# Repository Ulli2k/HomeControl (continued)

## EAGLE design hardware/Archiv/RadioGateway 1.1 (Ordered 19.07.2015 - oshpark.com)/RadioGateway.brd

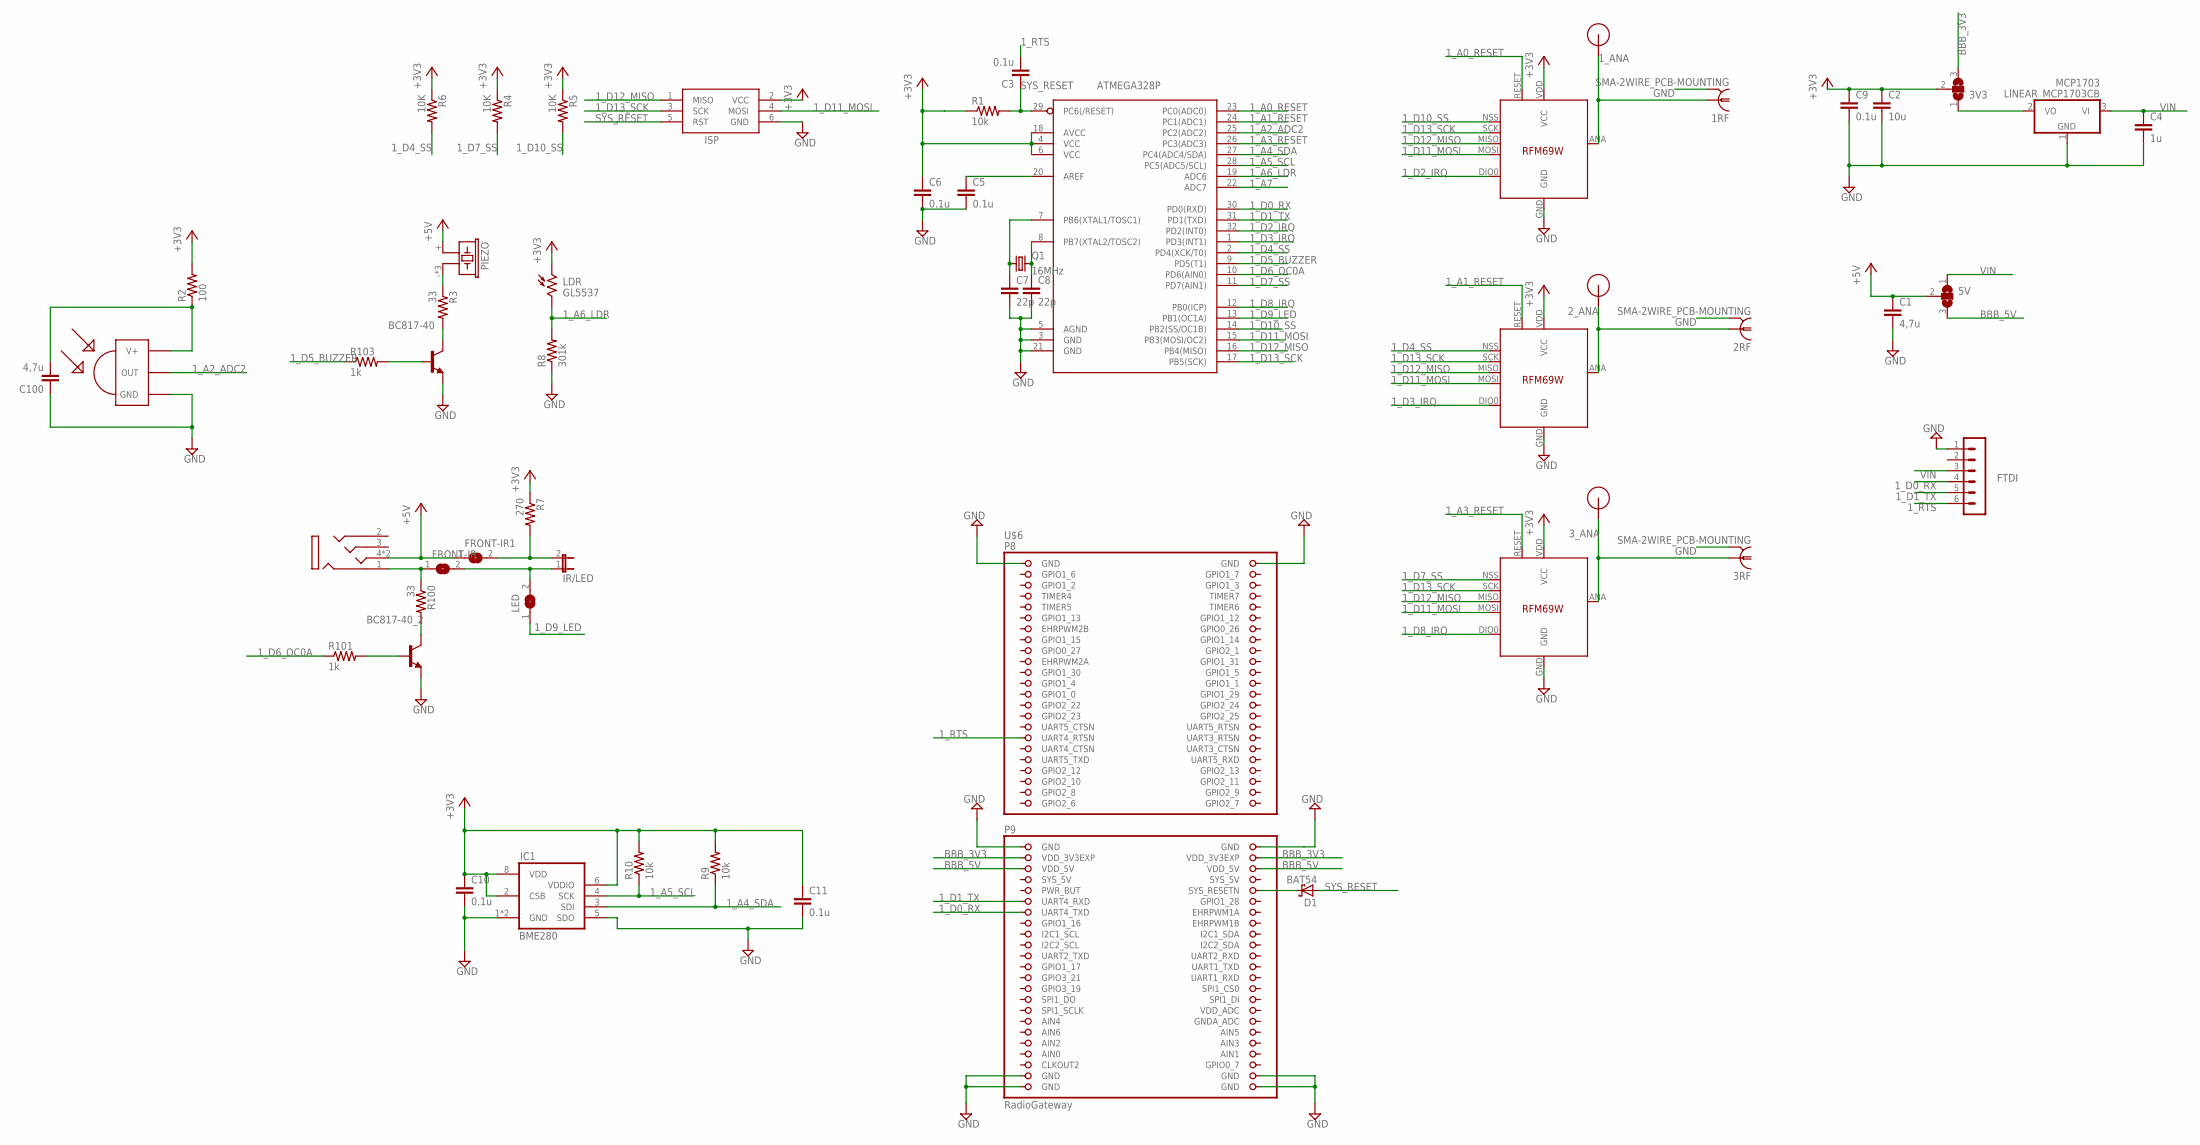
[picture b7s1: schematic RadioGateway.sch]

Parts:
1RF, 2RF, 3RF: SMA-2WIRE_PCB-MOUNTING; J01151A0931
1_RFM69, 2_RFM69, 3_RFM69: RFM69_MINIPADS; RFM69W-MINPADS
3V3, 5V: SJ2W; SJ_2
ATMEGA328P: ATMega-328; TQFP32-08
BC817-40, BC817-40_2: BC817-40-NPN-SOT23-BEC; SOT23-BEC
C1, C100: 4,7u; 0603-CAP
C2: 10u; 0603-CAP
C3, C5, C6, C9, C10, C11: 0.1u; 0603-CAP
C4: 1u; 0603-CAP
C7, C8: 22p; 0603-CAP
D1: BAT54; SOT23
FRONT-IR, FRONT-IR1: SJ
FTDI: FTDI; MA06-1
IC1: BME280
IR-RX: TSOP4836; TSOP18XX
IR-TX: 1503_13; 1503-03
IR/LED: JP1E; JP1
ISP: AVRISP-6; AVRISP
LDR: GL5537; M9960
LED: SJ
MCP1703: LINEAR_MCP1703CB; LINEAR_SOT23
PIEZO: BUZZER-PIEZO_SMD
Q1: 16MHz; HC49/S
R1, R9, R10: 10k; 0603-RES
R2: 100; 0603-RES
R3, R100: 33; 0603-RES
R4, R5, R6: 10K; 0603-RES
R7: 270; 0603-RES
R8: 301k; 0603-RES
R101, R103: 1k; 0603-RES
U$1, U$2, U$5: RFM12B_ANTENNA; RFM12B-ANTENNA
U$6: RadioGateway; BEAGLEBONE_SHIELD

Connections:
1_A0_RESET: 1_RFM69.RESET, ATMEGA328P.23 (PC0(ADC0))
1_A1_RESET: 2_RFM69.RESET, ATMEGA328P.24 (PC1(ADC1))
1_A2_ADC2: ATMEGA328P.25 (PC2(ADC2)), IR-RX.OUT
1_A3_RESET: 3_RFM69.RESET, ATMEGA328P.26 (PC3(ADC3))
1_A4_SDA: ATMEGA328P.27 (PC4(ADC4/SDA)), IC1.3 (SDI), R9.1
1_A5_SCL: ATMEGA328P.28 (PC5(ADC5/SCL)), IC1.4 (SCK), R10.1
1_A6_LDR: ATMEGA328P.19 (ADC6), LDR.2, R8.2
1_A7: ATMEGA328P.22 (ADC7)
1_ANA: 1RF.1, 1_RFM69.ANA (ANT), U$1.P$1
1_AREF: ATMEGA328P.20 (AREF), C5.1
1_D0_RX: ATMEGA328P.30 (PD0(RXD)), FTDI.4, U$6.59 (UART4_TXD)
1_D1_TX: ATMEGA328P.31 (PD1(TXD)), FTDI.5, U$6.57 (UART4_RXD)
1_D2_IRQ: 1_RFM69.DIO0 (DIO0/IRQ), ATMEGA328P.32 (PD2(INT0))
1_D3_IRQ: 2_RFM69.DIO0 (DIO0/IRQ), ATMEGA328P.1 (PD3(INT1))
1_D4_SS: 2_RFM69.NSS (SEL), ATMEGA328P.2 (PD4(XCK/T0)), R6.2
1_D5_BUZZER: ATMEGA328P.9 (PD5(T1)), R103.1
1_D6_OC0A: ATMEGA328P.10 (PD6(AIN0)), R101.1
1_D7_SS: 3_RFM69.NSS (SEL), ATMEGA328P.11 (PD7(AIN1)), R4.2
1_D8_IRQ: 3_RFM69.DIO0 (DIO0/IRQ), ATMEGA328P.12 (PB0(ICP))
1_D9_LED: ATMEGA328P.13 (PB1(OC1A)), LED.1
1_D10_SS: 1_RFM69.NSS (SEL), ATMEGA328P.14 (PB2(SS/OC1B)), R5.2
1_D11_MOSI: 1_RFM69.MOSI, 2_RFM69.MOSI, 3_RFM69.MOSI, ATMEGA328P.15 (PB3(MOSI/OC2)), ISP.4 (MOSI)
1_D12_MISO: 1_RFM69.MISO, 2_RFM69.MISO, 3_RFM69.MISO, ATMEGA328P.16 (PB4(MISO)), ISP.1 (MISO)
1_D13_SCK: 1_RFM69.SCK, 2_RFM69.SCK, 3_RFM69.SCK, ATMEGA328P.17 (PB5(SCK)), ISP.3 (SCK)
1_RTS: C3.2, FTDI.6, U$6.33 (UART4_RTSN)
2_ANA: 2RF.1, 2_RFM69.ANA (ANT), U$5.P$1
3_ANA: 3RF.1, 3_RFM69.ANA (ANT), U$2.P$1
+3V3: 1_RFM69.VDD (VCC), 2_RFM69.VDD (VCC), 3V3.2, 3_RFM69.VDD (VCC), ATMEGA328P.4 (VCC), ATMEGA328P.6 (VCC), ATMEGA328P.18 (AVCC), C2.1, C6.1, C9.1, C10.1, C11.1, IC1.2 (CSB), IC1.6 (VDDIO), IC1.8 (VDD), ISP.2 (VCC), LDR.1, R1.1, R2.2, R4.1, R5.1, R6.1, R7.1, R9.2, R10.2
+5V: 5V.2, C1.1, FRONT-IR1.1, IR-TX.4, IR-TX.4-2 (4), PIEZO.+ (1)
AIN0: U$6.85 (AIN0)
BBB_3V3: 3V3.3, U$6.49 (VDD_3V3EXP), U$6.50 (VDD_3V3EXP)
BBB_5V: 5V.3, U$6.51 (VDD_5V), U$6.52 (VDD_5V)
GND: 1RF.G@1 (2), 1RF.G@2 (2), 1RF.G@3 (2), 1RF.G@4 (2), 1_RFM69.GND, 2RF.G@1 (2), 2RF.G@2 (2), 2RF.G@3 (2), 2RF.G@4 (2), 2_RFM69.GND, 3RF.G@1 (2), 3RF.G@2 (2), 3RF.G@3 (2), 3RF.G@4 (2), 3_RFM69.GND, ATMEGA328P.3 (GND), ATMEGA328P.5 (AGND), ATMEGA328P.21 (GND), BC817-40.E, BC817-40_2.E, C1.2, C2.2, C4.2, C5.2, C6.2, C7.2, C8.2, C9.2, C10.2, C11.2, C100.1, FTDI.1, IC1.1 (GND), IC1.5 (SDO), IC1.7 (GND), IR-RX.GND, ISP.6 (GND), MCP1703.1 (GND), R8.1, U$6.1 (GND), U$6.2 (GND), U$6.47 (GND), U$6.48 (GND), U$6.89 (GND), U$6.90 (GND), U$6.91 (GND), U$6.92 (GND)
unnamed: ATMEGA328P.7 (PB6(XTAL1/TOSC1)), C7.1, Q1.1
unnamed: PIEZO.- (2), PIEZO.DUMMY (2), PIEZO.DUMMY1 (2), R3.1
unnamed: FRONT-IR.1, IR-TX.1, R100.1
unnamed: BC817-40_2.C, R100.2
unnamed: D1.3 (C), U$6.56 (SYS_RESETN)
unnamed: 3V3.1, MCP1703.2 (VO)
unnamed: ATMEGA328P.8 (PB7(XTAL2/TOSC2)), C8.1, Q1.2
unnamed: BC817-40.C, R3.2
unnamed: FRONT-IR.2, IR/LED.1, LED.2
unnamed: FRONT-IR1.2, IR/LED.2, R7.2
unnamed: BC817-40.B, R103.2
unnamed: C100.2, IR-RX.VCC (V+), R2.1
unnamed: BC817-40_2.B, R101.2
SYS_5V: U$6.53 (SYS_5V)
SYS_RESET: ATMEGA328P.29 (PC6(/RESET)), C3.1, D1.1 (A), ISP.5 (RST), R1.2
VIN: 5V.1, C4.1, FTDI.3, MCP1703.3 (VI)

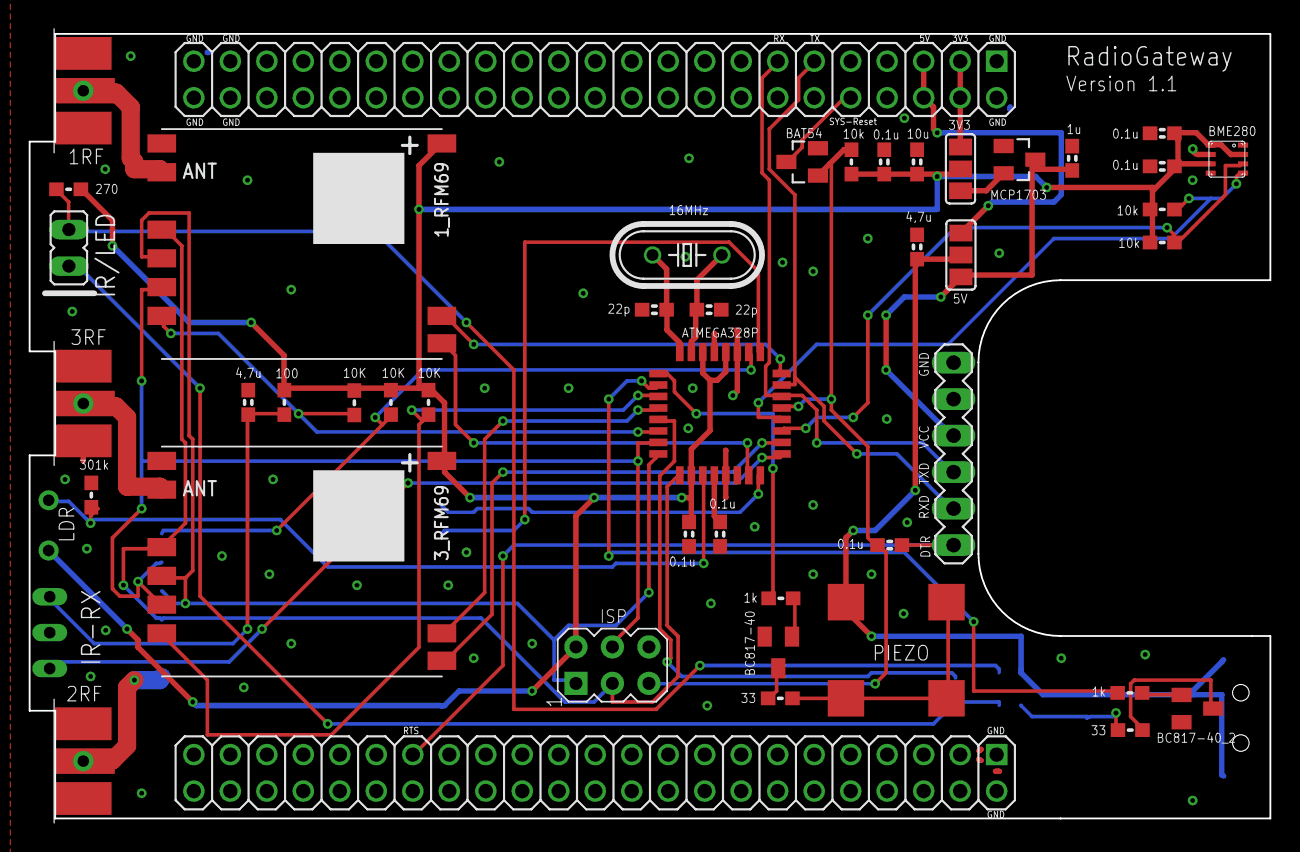
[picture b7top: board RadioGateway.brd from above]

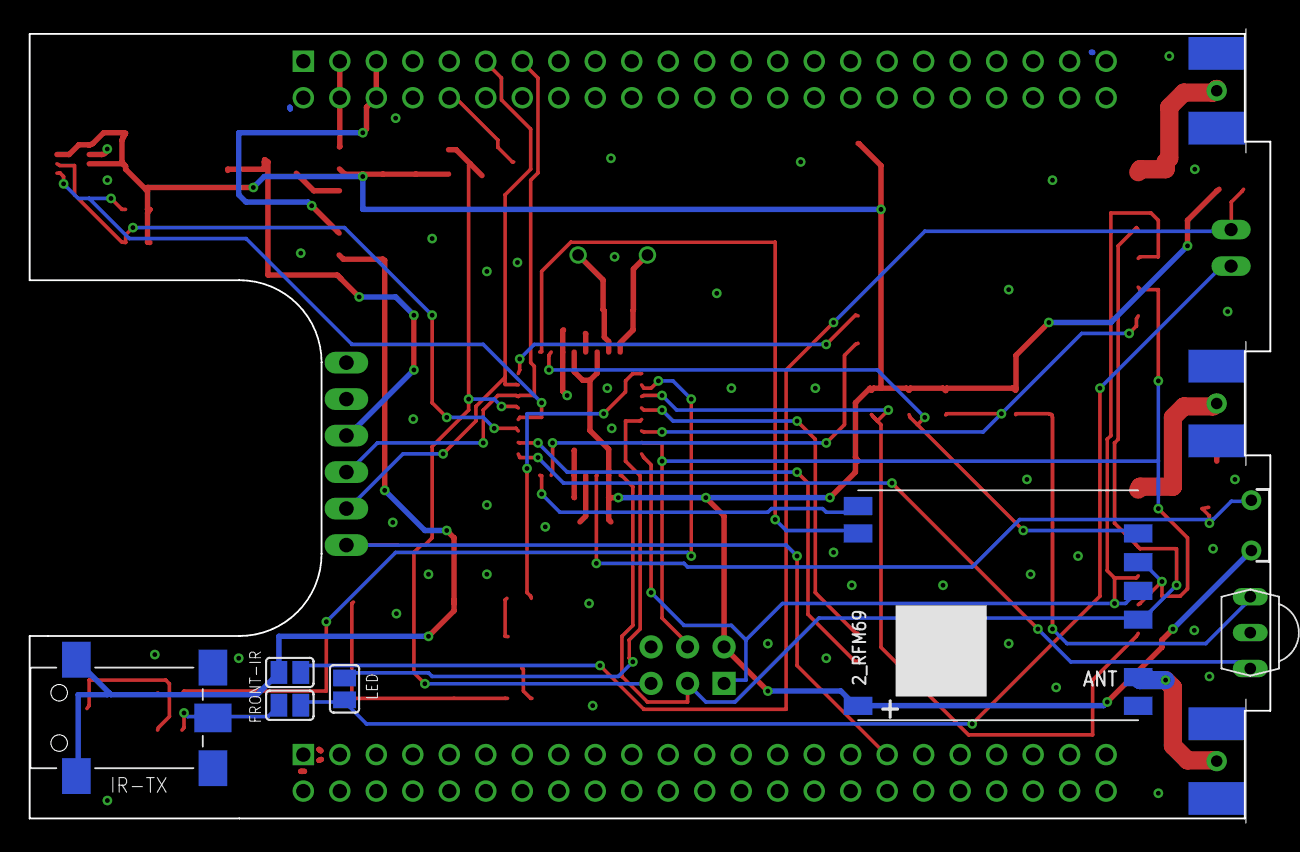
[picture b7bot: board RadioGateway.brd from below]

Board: 2 copper layers, 86.4 x 54.6 mm, 54 parts (7 on the bottom side), 46 nets.

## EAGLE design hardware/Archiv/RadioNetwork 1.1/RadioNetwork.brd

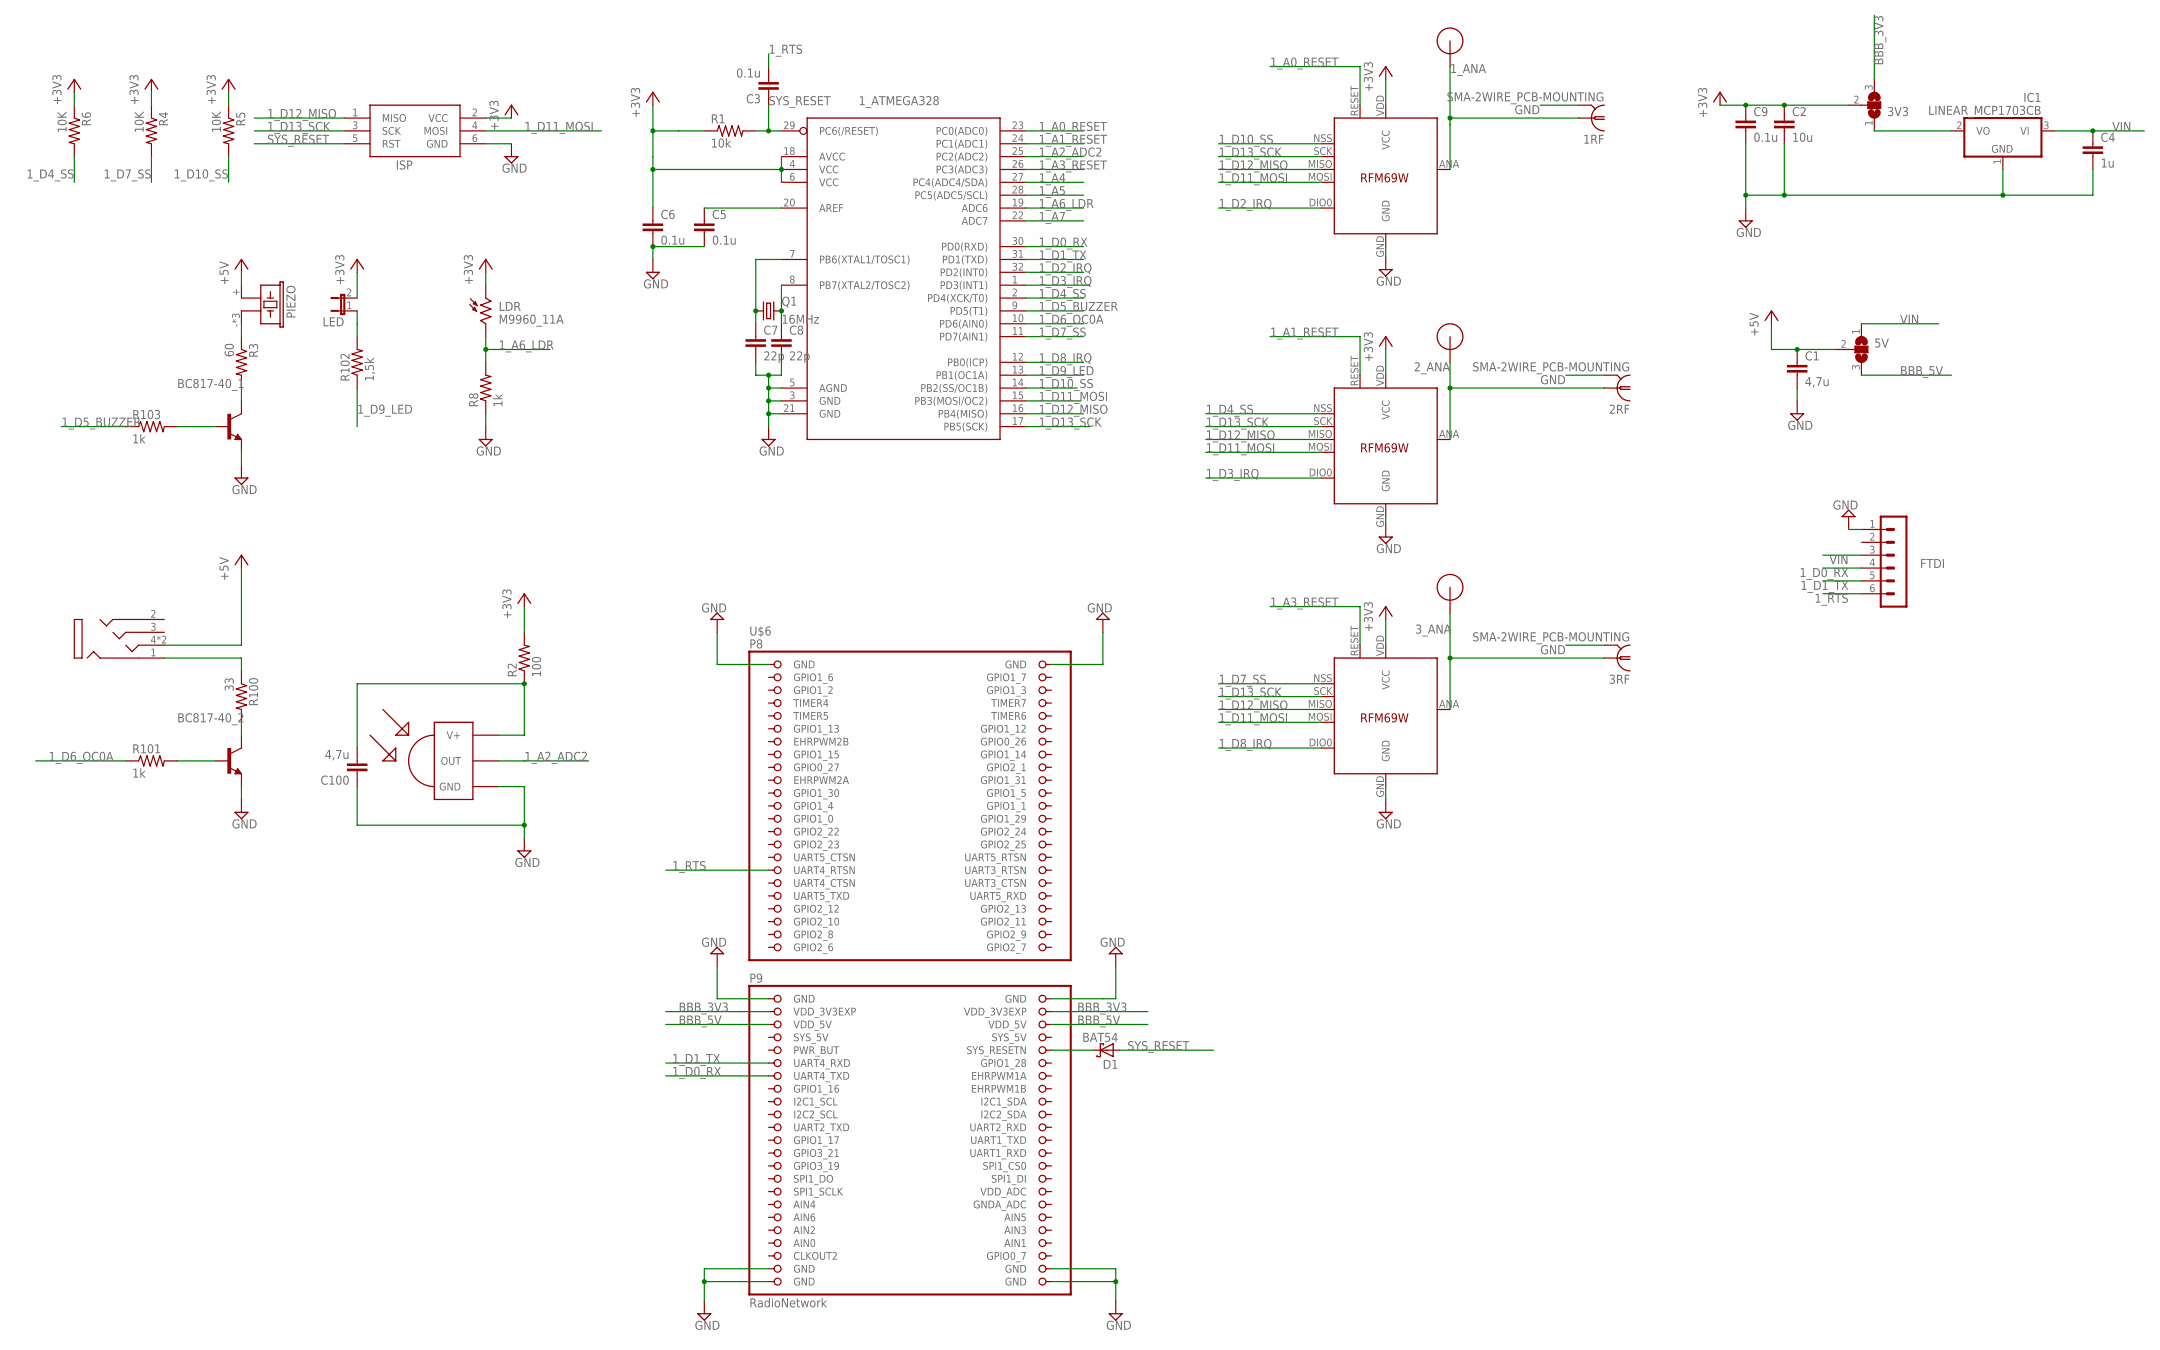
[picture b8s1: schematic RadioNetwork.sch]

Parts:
1RF, 2RF, 3RF: SMA-2WIRE_PCB-MOUNTING; J01151A0931
1_ATMEGA328: ATMega-328; TQFP32-08
1_RFM69, 2_RFM69, 3_RFM69: RFM69_MINIPADS; RFM69W-MINPADS
3V3, 5V: SJ2W; SJ_2
BC817-40_1, BC817-40_2: BC817-40-NPN-SOT23-BEC; SOT23-BEC
C1, C100: 4,7u; 0603-CAP
C2: 10u; 0603-CAP
C3, C5, C6, C9: 0.1u; 0603-CAP
C4: 1u; 0603-CAP
C7, C8: 22p; 0603-CAP
D1: BAT54; SOT23
FTDI: FTDI; MA06-1
IC1: LINEAR_MCP1703CB; LINEAR_SOT23
IR-RX: TSOP4836; TSOP18XX
IR-TX: 1503_13; 1503-03
ISP: AVRISP-6; AVRISP
LDR: M9960_11A; M9960
LED: JP1E; JP1
PIEZO: BUZZER-PIEZO_SMD
Q1: 16MHz; HC49/S
R1: 10k; 0603-RES
R2: 100; 0603-RES
R3: 60; 0603-RES
R4, R5, R6: 10K; 0603-RES
R8, R101, R103: 1k; 0603-RES
R100: 33; 0603-RES
R102: 1,5k; 0603-RES
U$1, U$2, U$5: RFM12B_ANTENNA; RFM12B-ANTENNA
U$6: RadioNetwork; BEAGLEBONE_SHIELD

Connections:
1_A0_RESET: 1_ATMEGA328.23 (PC0(ADC0)), 1_RFM69.RESET
1_A1_RESET: 1_ATMEGA328.24 (PC1(ADC1)), 2_RFM69.RESET
1_A2_ADC2: 1_ATMEGA328.25 (PC2(ADC2)), IR-RX.OUT
1_A3_RESET: 1_ATMEGA328.26 (PC3(ADC3)), 3_RFM69.RESET
1_A4: 1_ATMEGA328.27 (PC4(ADC4/SDA))
1_A5: 1_ATMEGA328.28 (PC5(ADC5/SCL))
1_A6_LDR: 1_ATMEGA328.19 (ADC6), LDR.2, R8.2
1_A7: 1_ATMEGA328.22 (ADC7)
1_ANA: 1RF.1, 1_RFM69.ANA (ANT), U$1.P$1
1_AREF: 1_ATMEGA328.20 (AREF), C5.1
1_D0_RX: 1_ATMEGA328.30 (PD0(RXD)), FTDI.4, U$6.59 (UART4_TXD)
1_D1_TX: 1_ATMEGA328.31 (PD1(TXD)), FTDI.5, U$6.57 (UART4_RXD)
1_D2_IRQ: 1_ATMEGA328.32 (PD2(INT0)), 1_RFM69.DIO0 (DIO0/IRQ)
1_D3_IRQ: 1_ATMEGA328.1 (PD3(INT1)), 2_RFM69.DIO0 (DIO0/IRQ)
1_D4_SS: 1_ATMEGA328.2 (PD4(XCK/T0)), 2_RFM69.NSS (SEL), R6.2
1_D5_BUZZER: 1_ATMEGA328.9 (PD5(T1)), R103.1
1_D6_OC0A: 1_ATMEGA328.10 (PD6(AIN0)), R101.1
1_D7_SS: 1_ATMEGA328.11 (PD7(AIN1)), 3_RFM69.NSS (SEL), R4.2
1_D8_IRQ: 1_ATMEGA328.12 (PB0(ICP)), 3_RFM69.DIO0 (DIO0/IRQ)
1_D9_LED: 1_ATMEGA328.13 (PB1(OC1A)), R102.1
1_D10_SS: 1_ATMEGA328.14 (PB2(SS/OC1B)), 1_RFM69.NSS (SEL), R5.2
1_D11_MOSI: 1_ATMEGA328.15 (PB3(MOSI/OC2)), 1_RFM69.MOSI, 2_RFM69.MOSI, 3_RFM69.MOSI, ISP.4 (MOSI)
1_D12_MISO: 1_ATMEGA328.16 (PB4(MISO)), 1_RFM69.MISO, 2_RFM69.MISO, 3_RFM69.MISO, ISP.1 (MISO)
1_D13_SCK: 1_ATMEGA328.17 (PB5(SCK)), 1_RFM69.SCK, 2_RFM69.SCK, 3_RFM69.SCK, ISP.3 (SCK)
1_RTS: C3.2, FTDI.6, U$6.33 (UART4_RTSN)
2_ANA: 2RF.1, 2_RFM69.ANA (ANT), U$5.P$1
3_ANA: 3RF.1, 3_RFM69.ANA (ANT), U$2.P$1
+3V3: 1_ATMEGA328.4 (VCC), 1_ATMEGA328.6 (VCC), 1_ATMEGA328.18 (AVCC), 1_RFM69.VDD (VCC), 2_RFM69.VDD (VCC), 3V3.2, 3_RFM69.VDD (VCC), C2.1, C6.1, C9.1, ISP.2 (VCC), LDR.1, LED.2, R1.1, R2.2, R4.1, R5.1, R6.1
+5V: 5V.2, C1.1, IR-TX.4, IR-TX.4-2 (4), PIEZO.+ (1)
AIN0: U$6.85 (AIN0)
BBB_3V3: 3V3.3, U$6.49 (VDD_3V3EXP), U$6.50 (VDD_3V3EXP)
BBB_5V: 5V.3, U$6.51 (VDD_5V), U$6.52 (VDD_5V)
GND: 1RF.G@1 (2), 1RF.G@2 (2), 1RF.G@3 (2), 1RF.G@4 (2), 1_ATMEGA328.3 (GND), 1_ATMEGA328.5 (AGND), 1_ATMEGA328.21 (GND), 1_RFM69.GND, 2RF.G@1 (2), 2RF.G@2 (2), 2RF.G@3 (2), 2RF.G@4 (2), 2_RFM69.GND, 3RF.G@1 (2), 3RF.G@2 (2), 3RF.G@3 (2), 3RF.G@4 (2), 3_RFM69.GND, BC817-40_1.E, BC817-40_2.E, C1.2, C2.2, C4.2, C5.2, C6.2, C7.2, C8.2, C9.2, C100.1, FTDI.1, IC1.1 (GND), IR-RX.GND, ISP.6 (GND), R8.1, U$6.1 (GND), U$6.2 (GND), U$6.47 (GND), U$6.48 (GND), U$6.89 (GND), U$6.90 (GND), U$6.91 (GND), U$6.92 (GND)
unnamed: 1_ATMEGA328.7 (PB6(XTAL1/TOSC1)), C7.1, Q1.1
unnamed: PIEZO.- (2), PIEZO.DUMMY (2), PIEZO.DUMMY1 (2), R3.1
unnamed: IR-TX.1, R100.1
unnamed: BC817-40_2.C, R100.2
unnamed: D1.3 (C), U$6.56 (SYS_RESETN)
unnamed: 3V3.1, IC1.2 (VO)
unnamed: 1_ATMEGA328.8 (PB7(XTAL2/TOSC2)), C8.1, Q1.2
unnamed: BC817-40_1.C, R3.2
unnamed: BC817-40_1.B, R103.2
unnamed: C100.2, IR-RX.VCC (V+), R2.1
unnamed: BC817-40_2.B, R101.2
unnamed: LED.1, R102.2
SYS_5V: U$6.53 (SYS_5V)
SYS_RESET: 1_ATMEGA328.29 (PC6(/RESET)), C3.1, D1.1 (A), ISP.5 (RST), R1.2
VIN: 5V.1, C4.1, FTDI.3, IC1.3 (VI)

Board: 2 copper layers, 46 parts (6 on the bottom side), 43 nets, no tracks yet.

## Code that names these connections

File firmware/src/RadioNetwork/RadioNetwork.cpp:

/*
avrdude -b 115200 -p m328p -c arduino -P net:beagle:4000 -Uflash:w:HomeControl.cpp.hex  #433MHz
avrdude -b 115200 -p m328p -c arduino -P net:beagle:5000 -Uflash:w:HomeControl.cpp.hex  #868MHz
nc beagle 4001
*/

#include <myTiming.h> //notwendig da es nur im BaseModule nicht reicht ?
#include <PinChangeInt.h> //notwendig da es nur im BaseModule nicht reicht ?

/*********************** Include all Modules *****************************/
#include <myBaseModule.h>
#include <RingBuffer.h>
DataFIFO_t DataRing;

#include <myDataProcessing.h>
myDataProcessing DataProc;

#if HAS_UART
  #include <myUart.h>
  myUart Remote(SER_BAUD, HW_UART);
#endif

#if HAS_AVR
  #include <myAVR.h>
  myAVR myAvr;
#endif

#if HAS_ROLLO
	#include <myRollo.h>
	myROLLO myRollo;
#endif
	
#if HAS_IR_TX || HAS_IR_RX
  #include <myIRMP.h>
  myIRMP myIrmp;
#endif

#if HAS_BME280
  #include <Wire.h> 
  #include <myBME280.h>
  myBME280 myBME;
#endif

#if HAS_POWER_MONITOR_CT || HAS_POWER_MONITOR_PULSE
	#include <myPowerMonitor.h>
	myPOWERMONITOR myPowerMonitor;	
#endif


#if HAS_SPI && HAS_RFM69
  #include <mySPI.h>
  mySPI mySpi;
  //PROGMEM http://www.arduino.cc/en/Reference/PROGMEM
  //http://www.avrfreaks.net/index.php?name=PNphpBB2&file=viewtopic&t=38003
  const typeSPItable SPITab[] = {
  //{ ID              , SS           , SPI-IRQ, IRQ_InterruptType }
    { SPI_CONFIG_ID_1 , 10 /*PB2*/, INTZero /*PD2:INT0*/	, Interrupt_Rising },
	#if HAS_RFM69>=2
    { SPI_CONFIG_ID_2 , 4	 /*PD4*/, INTOne	/*PD4:INT1*/	, Interrupt_Rising },
  #endif
  #if HAS_RFM69>=3
    { SPI_CONFIG_ID_3 , 7	 /*PD7*/, 8				/*PB0:PINCHG*/, Interrupt_Rising },
  #endif
  #if HAS_RFM69>=4
  	/* ACHTUNG!! doppelter PinChangeInterrupt geht aktuell nur mit Pin 6 */
    { SPI_CONFIG_ID_4 , A5/*ADC5*/, 6				/*PD6:PINCHG*/, Interrupt_Rising },
  #endif
    { SPI_CONFIG_ID_INVALID, 0, 0, Interrupt_Off   },
  };

  #include <myRFM69.h>
  myRFM69 myRFM69_1(SPI_CONFIG_ID_1, A0 /*Reset*/,true /*HighPower*/,RFM69_PROTOCOL_MyProtocol);	//868MHz - top
  #if HAS_RFM69>=2
  myRFM69 myRFM69_2(SPI_CONFIG_ID_2, A1 /*ADC1*/,true /*HighPower*/,RFM69_PROTOCOL_MyProtocol); //868MHz - bottom
  #endif
  #if HAS_RFM69>=3
  myRFM69 myRFM69_3(SPI_CONFIG_ID_3, A3 /*ADC3*/,true /*HighPower*/,RFM69_PROTOCOL_MyProtocol); 	//868MHz - top
  #endif
  #if HAS_RFM69>=4
  myRFM69 myRFM69_4(SPI_CONFIG_ID_4, A4 /*ADC4*/,true /*HighPower*/,RFM69_PROTOCOL_HX2262); 		//433MHz - top
  #endif
#endif

/*********************** Modules Table *****************************/

const typeModuleInfo ModuleTab[] = {
  { MODULE_DATAPROCESSING   ,"qvhwW"    			, &DataProc }, //immer am Anfang


#if HAS_UART  
  { MODULE_SERIAL           ,""       			, &Remote   },
#endif

#if HAS_AVR
  { MODULE_AVR              ,"mdopCAlabSN"   , &myAvr    },
#endif

#if HAS_ROLLO
  { MODULE_ROLLO              ,"J"   				 , &myRollo  },
#endif

#if HAS_IR_TX || HAS_IR_RX
  { MODULE_IRMP             ,"I"     				, &myIrmp   },
#endif

#if HAS_BME280
  { MODULE_BME280           ,"E"     			 , &myBME   },
#endif

#if HAS_POWER_MONITOR_CT || HAS_POWER_MONITOR_PULSE
	{ MODULE_POWERMONITOR			,"P"					, &myPowerMonitor	},
#endif


// RFM immer am Schluss für Tunneling
#if HAS_RFM69
  { MODULE_SPI              ,""       		, &mySpi    },
  { MODULE_RFM69            ,"RfT" 				, &myRFM69_1   }, 	//868Mhz - top
	#if HAS_RFM69>=2
  { MODULE_RFM69            ,"RfT" 				, &myRFM69_2   }, //868Mhz - bottom
 	#endif
 	#if HAS_RFM69>=3
  { MODULE_RFM69            ,"RfT" 				, &myRFM69_3   }, //868Mhz - top
  #endif
 	#if HAS_RFM69>=4
  { MODULE_RFM69            ,"RfT" 				, &myRFM69_4   }, //433Mhz - top
	#endif
#endif

  { -1, "", NULL }
};

/*********************** MAIN Function *****************************/
void setup() {
  //First of all initialize everything
  const typeModuleInfo* pmt = ModuleTab;
  while(pmt->typecode >= 0) {
    pmt->module->initialize();
    pmt++;
  }
}

void loop() {
  const typeModuleInfo* pmt = ModuleTab;
  
#if HAS_INFO_POLL
  bool infoPoll;
  byte preScaler=0;
  infoPoll = myBaseModule::infoPollCycles(false,&preScaler);
#endif
  
  while(pmt->typecode >= 0) {
  	
	#if HAS_INFO_POLL
  	if(infoPoll) {
  		pmt->module->infoPoll(preScaler);
  	}
  	
  	if(pmt->module->poll() || infoPoll) {
	#else
		if(pmt->module->poll()) {
 	#endif

    #if HAS_LEDs && defined(LED_ACTIVITY)
      myAVR::activityLed(1);
    #endif
		#if HAS_POWER_OPTIMIZATIONS	
			myBaseModule::idleCycles(1); //is FIFO empty and idle time over?
		#endif
    }
    
    pmt++;
  }
}

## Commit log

2017-11-10 Create test
2017-11-11 Wakupsignal ergänzt
2017-11-11 Korrektur: Relativpfad in Makefile WakeupSignal für Tunneling Satellites
2017-11-18 ESP Flash Over WLAN in mk Files erweitert
2017-11-28 Update myBaseModule.h
    Print Message during RingBuffer overrun. (Debugging)
2017-11-28 Update myTiming.cpp
    millis_since added to consider timer counter overflows
2017-12-13 RingBuffer Überlauf Debug Bug
2018-04-02 Notwendige Anpassung für STM32.
2018-07-03 Umbau auf Klassen und Libraries
2018-07-20 C++ template Umbau ATSAMD und ATmega lauffähig
2018-07-21 Integration Functions Charakter in die Class Module.
2018-07-21 Umbau BME280 und export LibI2C
2018-07-22 SAMD: Sleep integriert und Wakeup über Interrupt integriert
2018-08-25 Cleanup Defines & BugFix RFM Reset for ATSAMD21
2018-08-25 Cleanup Tunneling/Forward Function (myDataProcessing & myRadio) Cleanup Defines
2018-08-25 ATSAMD21 LowPower Mode with RTC Wakeup & InfoPoll über SysClock (AlarmClass)
2018-08-25 Integrate SysClock Function incl. Sleeptime correction and modify lowPower for SAMD21
2018-09-11 Rollo Ergänzung und Aufsplittung digitalPin Class
2018-09-11 Rolle ergänzt
